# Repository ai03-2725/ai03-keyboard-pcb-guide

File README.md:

# ai03's Keyboard PCB guide

* The guide covers everything from installing KiCad to producing the PCB.
* [Read it here](https://wiki.ai03.com/books/pcb-design/chapter/pcb-designer-guide)

### Repo contents
The repository contains the latest version of a PCB built following the guide.
Feel free to take a look if you need some help.

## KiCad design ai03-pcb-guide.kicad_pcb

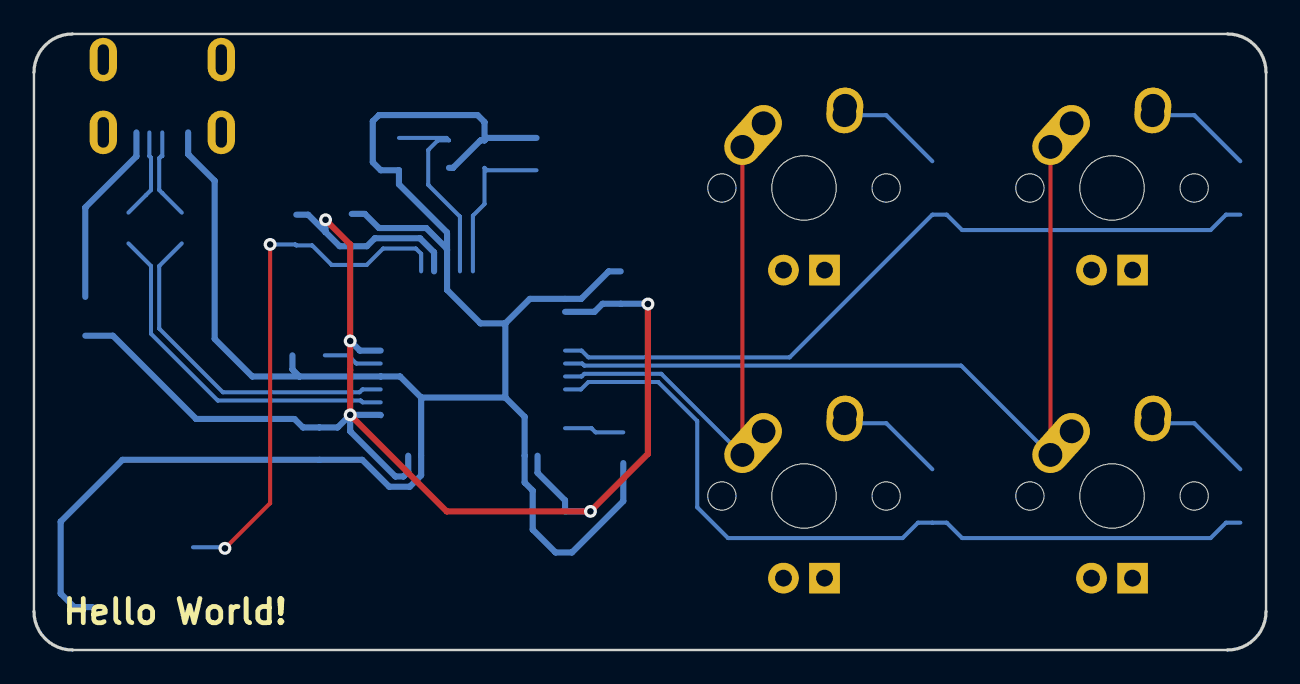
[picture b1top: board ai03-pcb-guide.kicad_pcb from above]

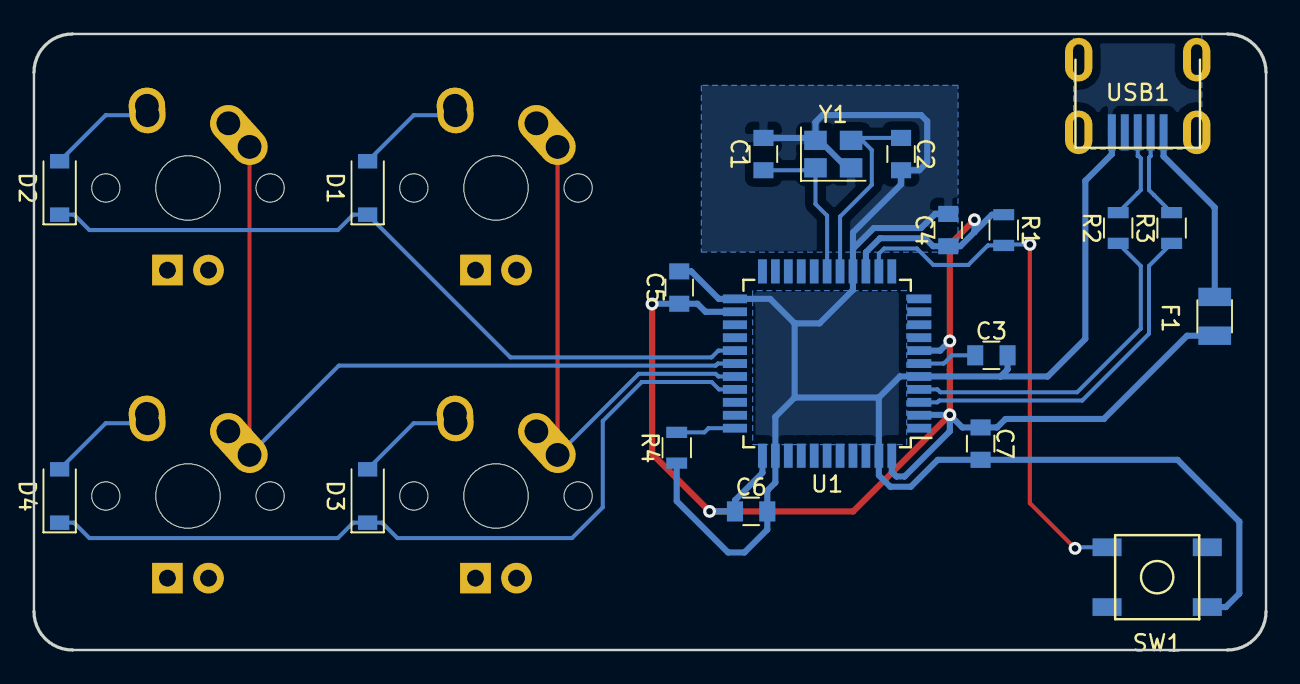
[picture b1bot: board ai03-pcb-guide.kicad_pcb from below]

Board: 2 copper layers, 76.2 x 38.1 mm, 24 parts (20 on the bottom side), 20 nets.

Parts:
C1, C2: 22pF; C_0805
C3: 1uF; C_0805
C4, C5, C6: 0.1uF; C_0805
C7: 10uF; C_0805
D1, D2, D3, D4: SOD-123; D_SOD-123
F1: 500mA; Fuse_SMD1206_Reflow
MX1, MX2, MX3, MX4: MX-1U
R1, R4: 10k; R_0805
R2, R3: 22; R_0805
SW1: SW_Push; SKQG-1155865
U1: ATmega32U4-AU; TQFP-44_10x10mm_Pitch0.8mm
USB1: Molex-0548190589; Molex-0548190589-Assembly
Y1: 16MHz; Crystal_SMD_3225-4pin_3.2x2.5mm

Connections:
+5V: C4.1, C5.1, C6.1, C7.1, F1.1, R1.1, U1.2, U1.7, U1.14, U1.24, U1.34, U1.44
COL0: MX1.1, MX3.1, U1.29
COL1: MX2.1, MX4.1, U1.28
D+: R2.2, USB1.3
D-: R3.2, USB1.4
GND: C1.2, C2.2, C3.2, C4.2, C5.2, C6.2, C7.2, R4.1, SW1.1, U1.5, U1.15, U1.23, U1.35, U1.43, USB1.1, Y1.2, Y1.4
unnamed: C1.1, U1.17, Y1.1
unnamed: C2.1, U1.16, Y1.3
unnamed: C3.1, U1.6
unnamed: D1.2, MX1.2
unnamed: D2.2, MX2.2
unnamed: D3.2, MX3.2
unnamed: D4.2, MX4.2
unnamed: R1.2, SW1.2, U1.13
unnamed: R2.1, U1.4
unnamed: R3.1, U1.3
unnamed: R4.2, U1.33
ROW0: D1.1, D2.1, U1.27
ROW1: D3.1, D4.1, U1.30
VCC: F1.2, USB1.5

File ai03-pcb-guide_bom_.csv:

Component,Description,Part,References,Value,Footprint,Quantity Per PCB,Datasheet
1,Unpolarized capacitor,C_Small,C4 C5 C6,0.1uF,C_0805,3,~
2,Unpolarized capacitor,C_Small,C7,10uF,C_0805,1,~
3,Unpolarized capacitor,C_Small,C3,1uF,C_0805,1,~
4,Unpolarized capacitor,C_Small,C1 C2,22pF,C_0805,2,~
5,"Diode, small symbol",D_Small,D1 D2 D3 D4,SOD-123,D_SOD-123,4,~
6,"resettable fuse, polymeric positive temperature coefficient (PPTC), small symbol",Polyfuse_Small,F1,500mA,Fuse_SMD1206_Reflow,1,~
7,,MX-1U,MX1 MX2 MX3 MX4,MX-1U,MX-1U,4,
8,"Resistor, small symbol",R_Small,R1 R4,10k,R_0805,2,~
9,"Resistor, small symbol",R_Small,R2 R3,22,R_0805,2,~
10,"Push button switch, generic, two pins",SW_Push,SW1,SW_Push,SKQG-1155865,1,
11,"16MHz, 16kB Flash, 1.25kB SRAM, 512B EEPROM, USB 2.0, TQFP-44",ATmega32U4-AU,U1,ATmega32U4-AU,TQFP-44_10x10mm_Pitch0.8mm,1,http://ww1.microchip.com/downloads/en/DeviceDoc/Atmel-7766-8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
12,,Molex-0548190589,USB1,Molex-0548190589,Molex-0548190589-Assembly,1,
13,"Four pin crystal, two ground/package pins (pin2 and 4) small symbol",Crystal_GND24_Small,Y1,16MHz,Crystal_SMD_3225-4pin_3.2x2.5mm,1,~
,,,,,,,
,,,,,,,
,,,,,,,
,,,,,,,
,,,,,,,
Component Groups:,13,,,,,,
Component Count:,24,,,,,,
Fitted Components:,24,,,,,,
Number of PCBs:,1,,,,,,
Total components:,24,,,,,,
Schematic Version:,,,,,,,
Schematic Date:,,,,,,,
BoM Date:,1/7/2019 21:46,,,,,,
Schematic Source:,,,,,,,
KiCad Version:,Eeschema (5.0.0),,,,,,

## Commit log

2019-01-07 Initialize project
2019-01-07 Add submodules
2019-01-08 Module update
2019-01-08 Add footprint libraries
2019-01-08 Finish schem
2019-01-08 Route PCB
2019-01-08 Generate gerbers
2019-01-08 Generate BOM
2019-05-27 Update to KiCad 5.1.2 guide data
2019-06-02 Update submodules to latest
2019-06-02 Progress
2019-06-02 Attempt remove submod
2019-06-02 re-add MX lib
2019-06-02 Update PCB for revised guide
2019-06-02 Finalize
2019-06-02 New gerbers
2022-05-14 fix(README): The design guide URL has changed
    The link in the current readme is pointed to an invalid subdomain of the ai03 website. I tracked down the correct URL and updated it.
